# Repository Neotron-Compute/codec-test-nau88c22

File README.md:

# NAU88C22 CODEC Test PCB

This is a PCB for testing the [Nuvoton NAU88C22 CODEC chip].

[Nuvoton NAU88C22 CODEC chip]: https://www.nuvoton.com/products/smart-home-audio/audio-converters/audio-codec-series/nau88c22yg/

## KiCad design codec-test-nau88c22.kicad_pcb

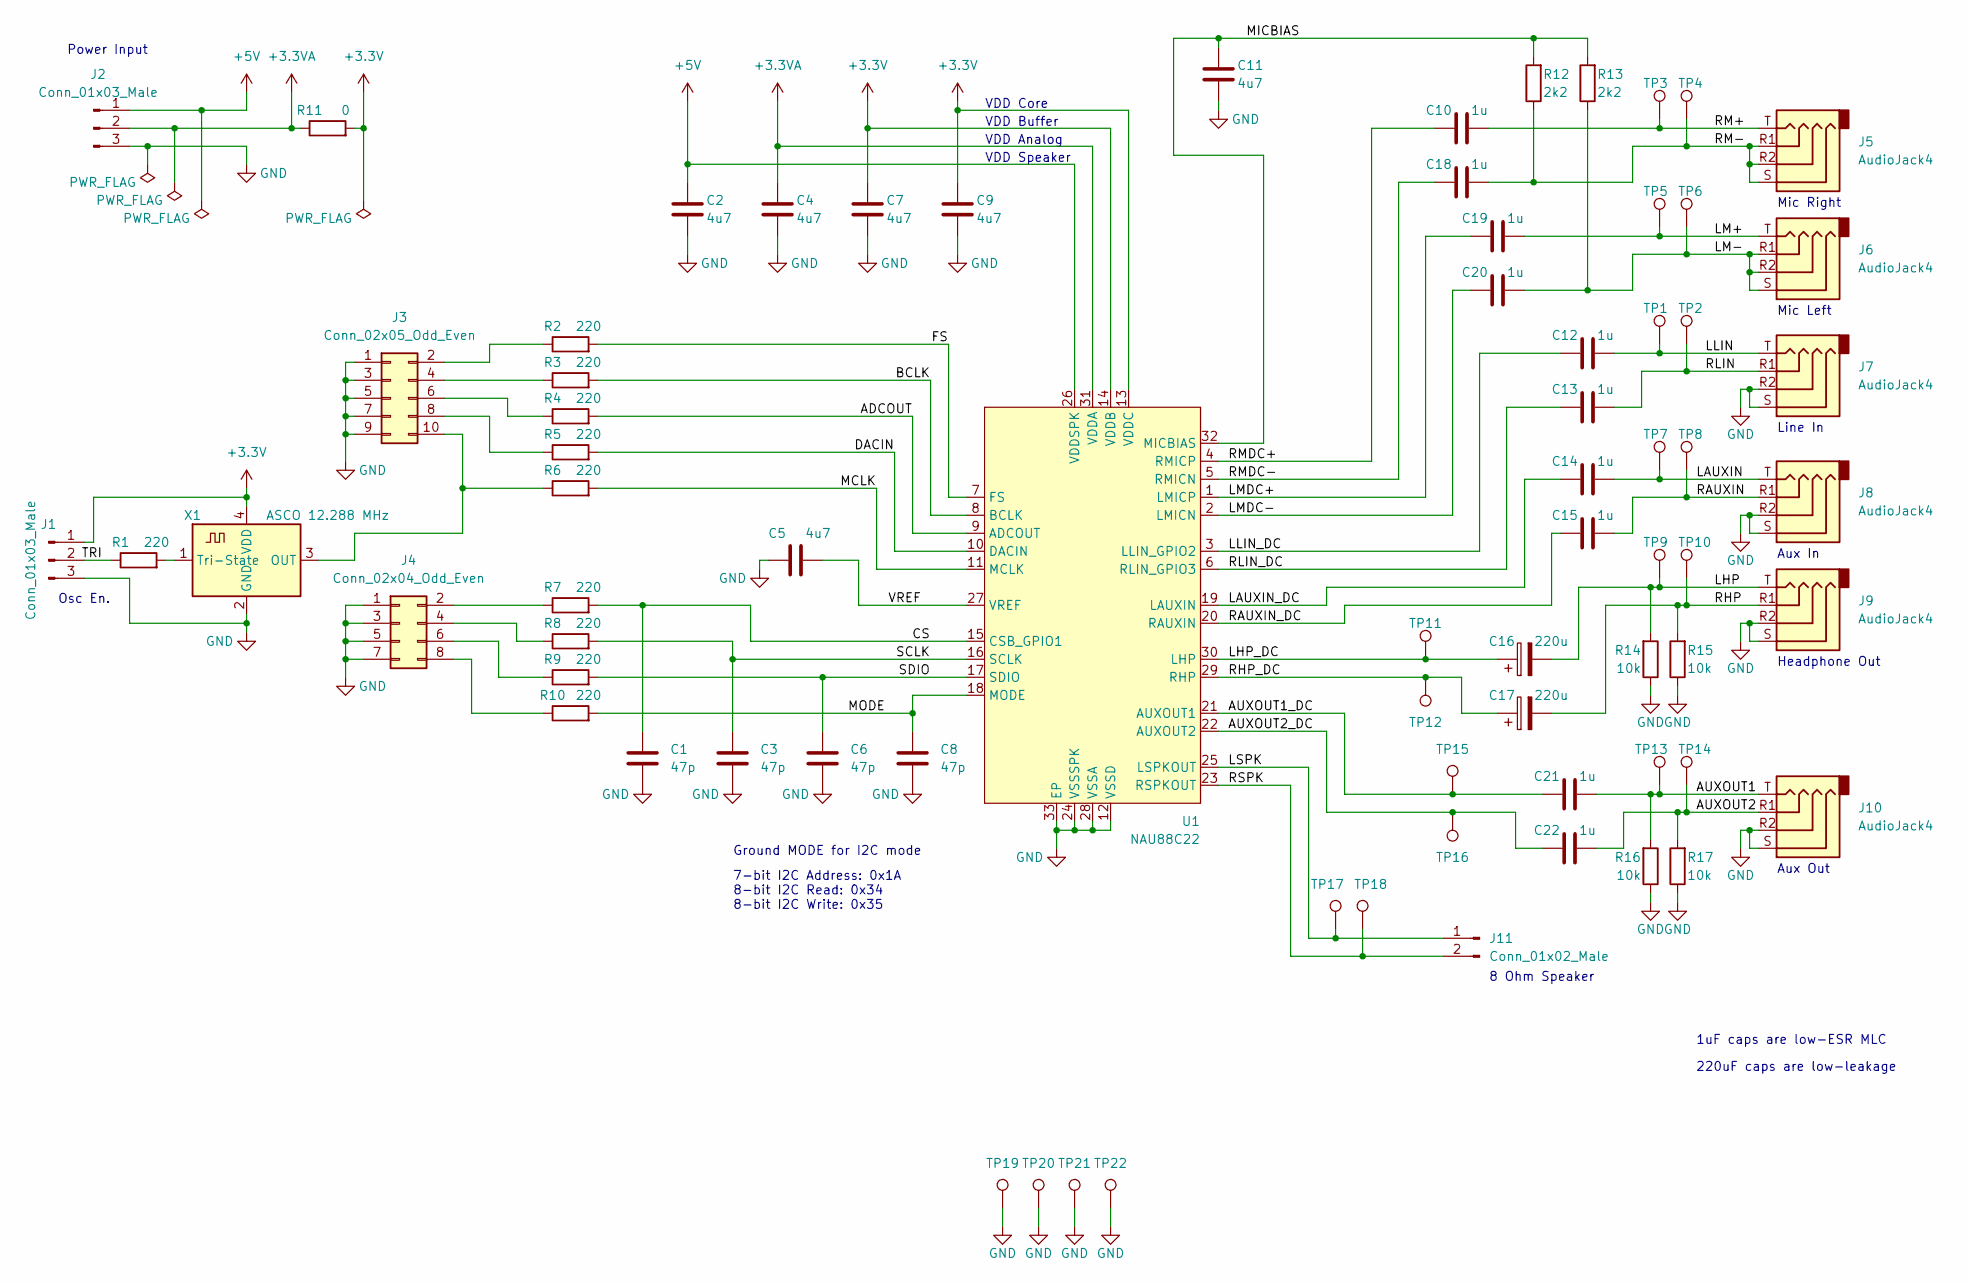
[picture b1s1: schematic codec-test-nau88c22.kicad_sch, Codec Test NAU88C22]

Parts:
C1, C3, C6, C8: 47p; C_0805_2012Metric; Part No CL21C470JBANNNC; LCSC Part# C14857
C2, C4, C5, C7, C9, C11: 4u7; C_0805_2012Metric; Part No CL21A475KAQNNNE; LCSC Part# C1779
C10, C12, C13, C14, C15, C18, C19, C20, C21, C22: 1u; C_0805_2012Metric; Part No CL21B105KBFNNNE; LCSC Part# C28323
C16, C17: 220u; CP_Elec_10x10; Part No UWT1H221MNL1GS; LCSC Part# C125977
J1, J2: Conn_01x03_Male; PinHeader_1x03_P2.54mm_Vertical
J3: Conn_02x05_Odd_Even; PinHeader_2x05_P2.54mm_Vertical
J4: Conn_02x04_Odd_Even; PinHeader_2x04_P2.54mm_Vertical
J5, J6, J7, J8, J9, J10: AudioJack4; Jack_3.5mm_PJ320D_Horizontal; Part No PJ-320D; LCSC Part# C431535
J11: Conn_01x02_Male; PinHeader_1x02_P2.54mm_Vertical
R1, R2, R3, R4, R5, R6, R7, R8, R9, R10: 220; R_0805_2012Metric; Part No 0805W8F2200T5E; LCSC Part# C17557
R11: 0; R_0805_2012Metric; Part No 0805W8F0000T5E; LCSC Part# C17477
R12, R13: 2k2; R_0805_2012Metric; Part No 0805W8F2201T5E; LCSC Part# C17520
R14, R15, R16, R17: 10k; R_0805_2012Metric; Part No 0805W8F1002T5E; LCSC Part# C17414
TP1, TP2, TP3, TP4, TP5, TP6, TP7, TP8, TP9, TP10, TP11, TP12, TP13, TP14, TP15, TP16, TP17, TP18, TP19, TP20, TP21, TP22: TestPoint; TestPoint_THTPad_2.0x2.0mm_Drill1.0mm
U1: NAU88C22; VQFN-32-1EP_5x5mm_P0.5mm_EP3.5x3.5mm; Part No NAU88C22YG; LCSC Part# C914209
X1: ASCO 12.288 MHz; Oscillator_SMD_Abracon_ASE-4Pin_3.2x2.5mm_HandSoldering; Part No OT2EL4C4JI-111OLP-12.288M; LCSC Part# C5203546

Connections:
+3.3V: C7.1, C9.1, J1.1, R11.2, U1.13 (VDDC), U1.14 (VDDB), X1.4 (VDD)
+3.3VA: C4.1, J2.2, R11.1, U1.31 (VDDA)
+5V: C2.1, J2.1, U1.26 (VDDSPK)
/ADCOUT: R4.2, U1.9 (ADCOUT)
/AUXOUT1: C21.2, J10.T, R16.2, TP13.1
/AUXOUT1_DC: C21.1, TP15.1, U1.21 (AUXOUT1)
/AUXOUT2: C22.2, J10.R1, R17.2, TP14.1
/AUXOUT2_DC: C22.1, TP16.1, U1.22 (AUXOUT2)
/BCLK: R3.2, U1.8 (BCLK)
/CS: C1.1, R7.2, U1.15 (CSB_GPIO1)
/DACIN: R5.2, U1.10 (DACIN)
/FS: R2.2, U1.7 (FS)
/LAUXIN: C14.2, J8.T, TP7.1
/LAUXIN_DC: C14.1, U1.19 (LAUXIN)
/LHP: C16.2, J9.T, R14.2, TP9.1
/LHP_DC: C16.1, TP11.1, U1.30 (LHP)
/LLIN: C12.2, J7.T, TP1.1
/LLIN_DC: C12.1, U1.3 (LLIN_GPIO2)
/LM+: C19.2, J6.T, TP5.1
/LM-: C20.2, J6.R1, J6.R2, J6.S, R13.1, TP6.1
/LMDC+: C19.1, U1.1 (LMICP)
/LMDC-: C20.1, U1.2 (LMICN)
/LSPK: J11.1, TP17.1, U1.25 (LSPKOUT)
/MCLK: R6.2, U1.11 (MCLK)
/MICBIAS: C11.1, R12.2, R13.2, U1.32 (MICBIAS)
/MODE: C8.1, R10.2, U1.18 (MODE)
/RAUXIN: C15.2, J8.R1, TP8.1
/RAUXIN_DC: C15.1, U1.20 (RAUXIN)
/RHP: C17.2, J9.R1, R15.2, TP10.1
/RHP_DC: C17.1, TP12.1, U1.29 (RHP)
/RLIN: C13.2, J7.R1, TP2.1
/RLIN_DC: C13.1, U1.6 (RLIN_GPIO3)
/RM+: C10.2, J5.T, TP3.1
/RM-: C18.2, J5.R1, J5.R2, J5.S, R12.1, TP4.1
/RMDC+: C10.1, U1.4 (RMICP)
/RMDC-: C18.1, U1.5 (RMICN)
/RSPK: J11.2, TP18.1, U1.23 (RSPKOUT)
/SCLK: C3.1, R8.2, U1.16 (SCLK)
/SDIO: C6.1, R9.2, U1.17 (SDIO)
/TRI: J1.2, R1.1
/VREF: C5.1, U1.27 (VREF)
GND: C1.2, C2.2, C3.2, C4.2, C5.2, C6.2, C7.2, C8.2, C9.2, C11.2, J1.3, J2.3, J3.1, J3.3, J3.5, J3.7, J3.9, J4.1, J4.3, J4.5, J4.7, J7.R2, J7.S, J8.R2, J8.S, J9.R2, J9.S, J10.R2, J10.S, R14.1, R15.1, R16.1, R17.1, TP19.1, TP20.1, TP21.1, TP22.1, U1.12 (VSSD), U1.24 (VSSSPK), U1.28 (VSSA), U1.33 (EP), X1.2 (GND)
unnamed: J3.2, R2.1
unnamed: J3.4, R3.1
unnamed: J3.6, R4.1
unnamed: J3.8, R5.1
unnamed: J3.10, R6.1, X1.3 (OUT)
unnamed: J4.2, R7.1
unnamed: J4.4, R8.1
unnamed: J4.6, R9.1
unnamed: J4.8, R10.1
unnamed: R1.2, X1.1 (Tri-State)

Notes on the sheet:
1uF caps are low-ESR MLC
Mic Right
Mic Left
Aux Out
7-bit I2C Address: 0x1A 8-bit I2C Read: 0x34 8-bit I2C Write: 0x35
VDD Analog
Headphone Out
Osc En.
Aux In
VDD Buffer
220uF caps are low-leakage
Power Input
8 Ohm Speaker
VDD Speaker
Line In
VDD Core
Ground MODE for I2C mode

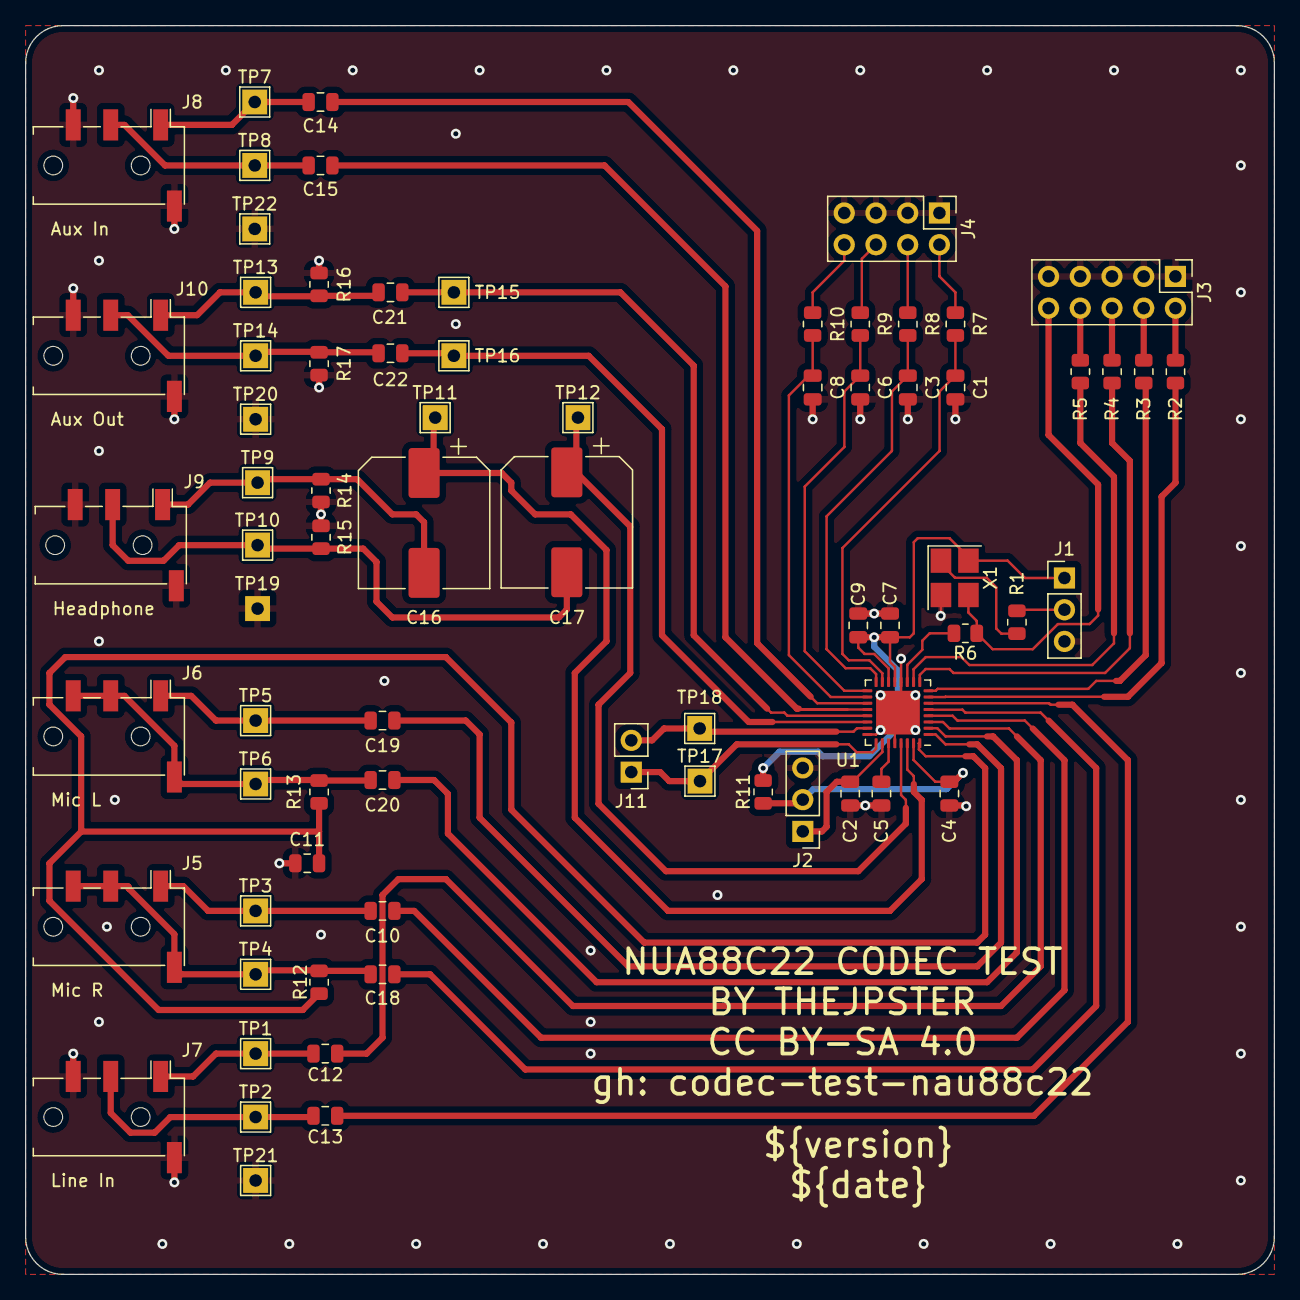
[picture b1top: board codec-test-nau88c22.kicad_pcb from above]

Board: 2 copper layers, 100.0 x 100.0 mm, 73 parts (0 on the bottom side), 52 nets.

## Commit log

2023-11-25 Intro
2023-11-25 First version
2023-11-25 Rewired then updated kibot
2023-11-25 Fix DRC errors
2023-12-16 Test program for RP2040.
    Currently incomplete.
2023-12-27 Makes incredibly loud static.
    But at least it plays something! I also
    added a simple UART interface to interactively poke registers.
2023-12-27 OK you can play audio....
    But I had to 'break' the PIO code to look for clock signals being the wrong way up in order for it to work. I worry that the PIO code is being encoded wrong. That or I just really can't read an oscil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
2023-12-29 Remove nightly, macOS and Windows builds.
    Ubuntu on stable Rust is fine.
2023-12-29 Use probe-rs-cli.
    It has a better progress bar.
2023-12-29 Put code back as it was and drop BCLK instead.
2023-12-29 Clean up imports.
2023-12-29 Use WAIT GPIO.
    Lower latency than wait pin, apparently.
2023-12-29 Turn on boost mode and RTL by default.
2023-12-29 Loop sample.
2024-01-26 Updated to released version of driver.

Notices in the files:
codec-test-nau88c22.kicad_pcb:
CC BY-SA 4.0
codec-test-nau88c22.kicad_sch:
Licensed as CC-BY-SA
Copyright (c) The Neotron Developers, 2023
